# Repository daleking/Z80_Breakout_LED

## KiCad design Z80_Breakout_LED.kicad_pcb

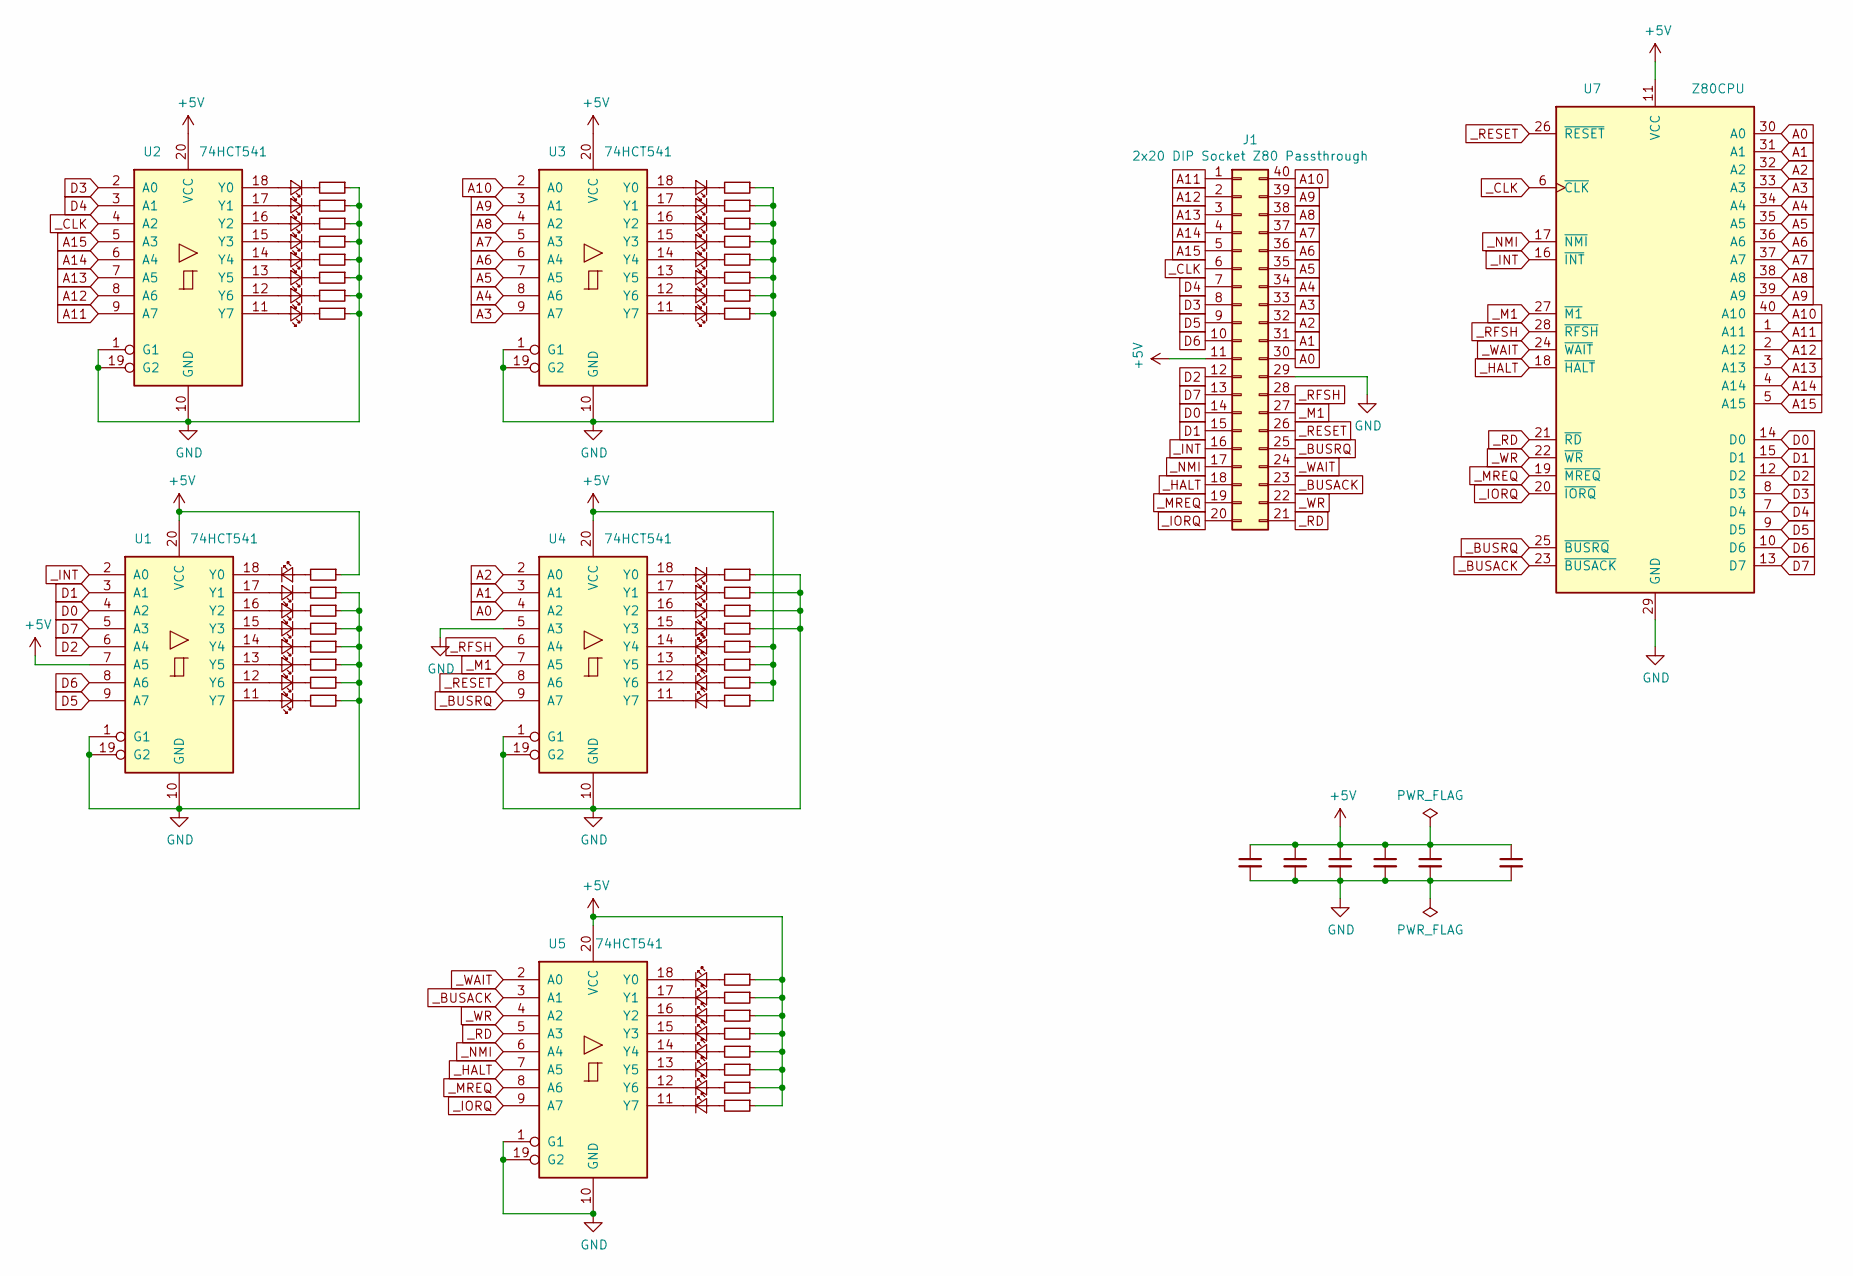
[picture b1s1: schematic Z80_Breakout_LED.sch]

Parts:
C1, C2, C3, C4, C5, C6: C_Small; C_Disc_D3.0mm_W2.0mm_P2.50mm
D1, D2, D3, D4, D5, D6, D7, D8, D9, D10, D11, D12, D13, D14, D15, D16, D17, D18, D19, D20, D21, D22, D23, D24, D25, D26, D27, D28, D29, D30, D31, D32, D33, D34, D35, D36, D37, D38, D39, D40: LED_Small; LED_D5.0mm
J1: 2x20 DIP Socket Z80 Passthrough; DIP-40_W15.24mm
R1, R2, R3, R4, R5, R6, R7, R8, R9, R10, R11, R12, R13, R14, R15, R16, R17, R18, R19, R20, R21, R22, R23, R24, R25, R26, R27, R28, R29, R30, R31, R32, R33, R34, R35, R36, R37, R38, R39, R40: R_Small; R_Axial_DIN0207_L6.3mm_D2.5mm_P10.16mm_Horizontal
U1, U2, U3, U4, U5: 74HCT541; DIP-20_W7.62mm_Socket
U7: Z80CPU; DIP-40_W15.24mm_Socket

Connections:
+5V: C1.1, C2.1, C3.1, C4.1, C5.1, C6.1, J1.11, R1.1, R29.1, R30.1, R31.1, R32.1, R33.1, R34.1, R35.1, R36.1, R37.1, R38.1, R39.1, R40.1, U1.7 (A5), U1.20 (VCC), U2.20 (VCC), U3.20 (VCC), U4.20 (VCC), U5.20 (VCC), U7.11 (VCC)
A0: J1.30, U4.4 (A2), U7.30 (A0)
A1: J1.31, U4.3 (A1), U7.31 (A1)
A2: J1.32, U4.2 (A0), U7.32 (A2)
A3: J1.33, U3.9 (A7), U7.33 (A3)
A4: J1.34, U3.8 (A6), U7.34 (A4)
A5: J1.35, U3.7 (A5), U7.35 (A5)
A6: J1.36, U3.6 (A4), U7.36 (A6)
A7: J1.37, U3.5 (A3), U7.37 (A7)
A8: J1.38, U3.4 (A2), U7.38 (A8)
A9: J1.39, U3.3 (A1), U7.39 (A9)
A10: J1.40, U3.2 (A0), U7.40 (A10)
A11: J1.1, U2.9 (A7), U7.1 (A11)
A12: J1.2, U2.8 (A6), U7.2 (A12)
A13: J1.3, U2.7 (A5), U7.3 (A13)
A14: J1.4, U2.6 (A4), U7.4 (A14)
A15: J1.5, U2.5 (A3), U7.5 (A15)
D0: J1.14, U1.4 (A2), U7.14 (D0)
D1: J1.15, U1.3 (A1), U7.15 (D1)
D2: J1.12, U1.6 (A4), U7.12 (D2)
D3: J1.8, U2.2 (A0), U7.8 (D3)
D4: J1.7, U2.3 (A1), U7.7 (D4)
D5: J1.9, U1.9 (A7), U7.9 (D5)
D6: J1.10, U1.8 (A6), U7.10 (D6)
D7: J1.13, U1.5 (A3), U7.13 (D7)
GND: C1.2, C2.2, C3.2, C4.2, C5.2, C6.2, J1.29, R2.1, R3.1, R4.1, R5.1, R6.1, R7.1, R8.1, R9.1, R10.1, R11.1, R12.1, R13.1, R14.1, R15.1, R16.1, R17.1, R18.1, R19.1, R20.1, R21.1, R22.1, R23.1, R24.1, R25.1, R26.1, R27.1, R28.1, U1.1 (G1), U1.10 (GND), U1.19 (G2), U2.1 (G1), U2.10 (GND), U2.19 (G2), U3.1 (G1), U3.10 (GND), U3.19 (G2), U4.1 (G1), U4.5 (A3), U4.10 (GND), U4.19 (G2), U5.1 (G1), U5.10 (GND), U5.19 (G2), U7.29 (GND)
unnamed: D1.1 (K), U1.18 (Y0)
unnamed: D1.2 (A), R1.2
unnamed: D2.1 (K), R2.2
unnamed: D2.2 (A), U1.17 (Y1)
unnamed: D3.1 (K), R3.2
unnamed: D3.2 (A), U1.16 (Y2)
unnamed: D4.1 (K), R4.2
unnamed: D4.2 (A), U1.15 (Y3)
unnamed: D5.1 (K), R5.2
unnamed: D5.2 (A), U1.14 (Y4)
unnamed: D6.1 (K), R6.2
unnamed: D6.2 (A), U1.13 (Y5)
unnamed: D7.1 (K), R7.2
unnamed: D7.2 (A), U1.12 (Y6)
unnamed: D8.1 (K), R8.2
unnamed: D8.2 (A), U1.11 (Y7)
unnamed: D9.1 (K), R9.2
unnamed: D9.2 (A), U2.18 (Y0)
unnamed: D10.1 (K), R10.2
unnamed: D10.2 (A), U2.17 (Y1)
unnamed: D11.1 (K), R11.2
unnamed: D11.2 (A), U2.16 (Y2)
unnamed: D12.1 (K), R12.2
unnamed: D12.2 (A), U2.15 (Y3)
unnamed: D13.1 (K), R13.2
unnamed: D13.2 (A), U2.14 (Y4)
unnamed: D14.1 (K), R14.2
unnamed: D14.2 (A), U2.13 (Y5)
unnamed: D15.1 (K), R15.2
unnamed: D15.2 (A), U2.12 (Y6)
unnamed: D16.1 (K), R16.2
unnamed: D16.2 (A), U2.11 (Y7)
unnamed: D17.1 (K), R17.2
unnamed: D17.2 (A), U3.18 (Y0)
unnamed: D18.1 (K), R18.2
unnamed: D18.2 (A), U3.17 (Y1)
unnamed: D19.1 (K), R19.2
unnamed: D19.2 (A), U3.16 (Y2)
unnamed: D20.1 (K), R20.2
unnamed: D20.2 (A), U3.15 (Y3)
unnamed: D21.1 (K), R21.2
unnamed: D21.2 (A), U3.14 (Y4)
unnamed: D22.1 (K), R22.2
unnamed: D22.2 (A), U3.13 (Y5)
unnamed: D23.1 (K), R23.2
unnamed: D23.2 (A), U3.12 (Y6)
unnamed: D24.1 (K), R24.2
unnamed: D24.2 (A), U3.11 (Y7)
unnamed: D25.1 (K), R25.2
unnamed: D25.2 (A), U4.18 (Y0)
unnamed: D26.1 (K), R26.2
unnamed: D26.2 (A), U4.17 (Y1)
unnamed: D27.1 (K), R27.2
unnamed: D27.2 (A), U4.16 (Y2)
unnamed: D28.1 (K), R28.2
unnamed: D28.2 (A), U4.15 (Y3)
unnamed: D29.1 (K), U4.14 (Y4)
unnamed: D29.2 (A), R29.2
unnamed: D30.1 (K), U4.13 (Y5)
unnamed: D30.2 (A), R30.2
unnamed: D31.1 (K), U4.12 (Y6)
unnamed: D31.2 (A), R31.2
unnamed: D32.1 (K), U4.11 (Y7)
unnamed: D32.2 (A), R32.2
unnamed: D33.1 (K), U5.18 (Y0)
unnamed: D33.2 (A), R33.2
unnamed: D34.1 (K), U5.17 (Y1)
unnamed: D34.2 (A), R34.2
unnamed: D35.1 (K), U5.16 (Y2)
unnamed: D35.2 (A), R35.2
unnamed: D36.1 (K), U5.15 (Y3)
unnamed: D36.2 (A), R36.2
unnamed: D37.1 (K), U5.14 (Y4)
unnamed: D37.2 (A), R37.2
unnamed: D38.1 (K), U5.13 (Y5)
unnamed: D38.2 (A), R38.2
unnamed: D39.1 (K), U5.12 (Y6)
unnamed: D39.2 (A), R39.2
unnamed: D40.1 (K), U5.11 (Y7)
unnamed: D40.2 (A), R40.2
_BUSACK: J1.23, U5.3 (A1), U7.23 (~BUSACK~)
_BUSRQ: J1.25, U4.9 (A7), U7.25 (~BUSRQ~)
_CLK: J1.6, U2.4 (A2), U7.6 (~CLK~)
_HALT: J1.18, U5.7 (A5), U7.18 (~HALT~)
_INT: J1.16, U1.2 (A0), U7.16 (~INT~)
_IORQ: J1.20, U5.9 (A7), U7.20 (~IORQ~)
_M1: J1.27, U4.7 (A5), U7.27 (~M1~)
_MREQ: J1.19, U5.8 (A6), U7.19 (~MREQ~)
_NMI: J1.17, U5.6 (A4), U7.17 (~NMI~)
_RD: J1.21, U5.5 (A3), U7.21 (~RD~)
_RESET: J1.26, U4.8 (A6), U7.26 (~RESET~)
_RFSH: J1.28, U4.6 (A4), U7.28 (~RFSH~)
_WAIT: J1.24, U5.2 (A0), U7.24 (~WAIT~)
_WR: J1.22, U5.4 (A2), U7.22 (~WR~)

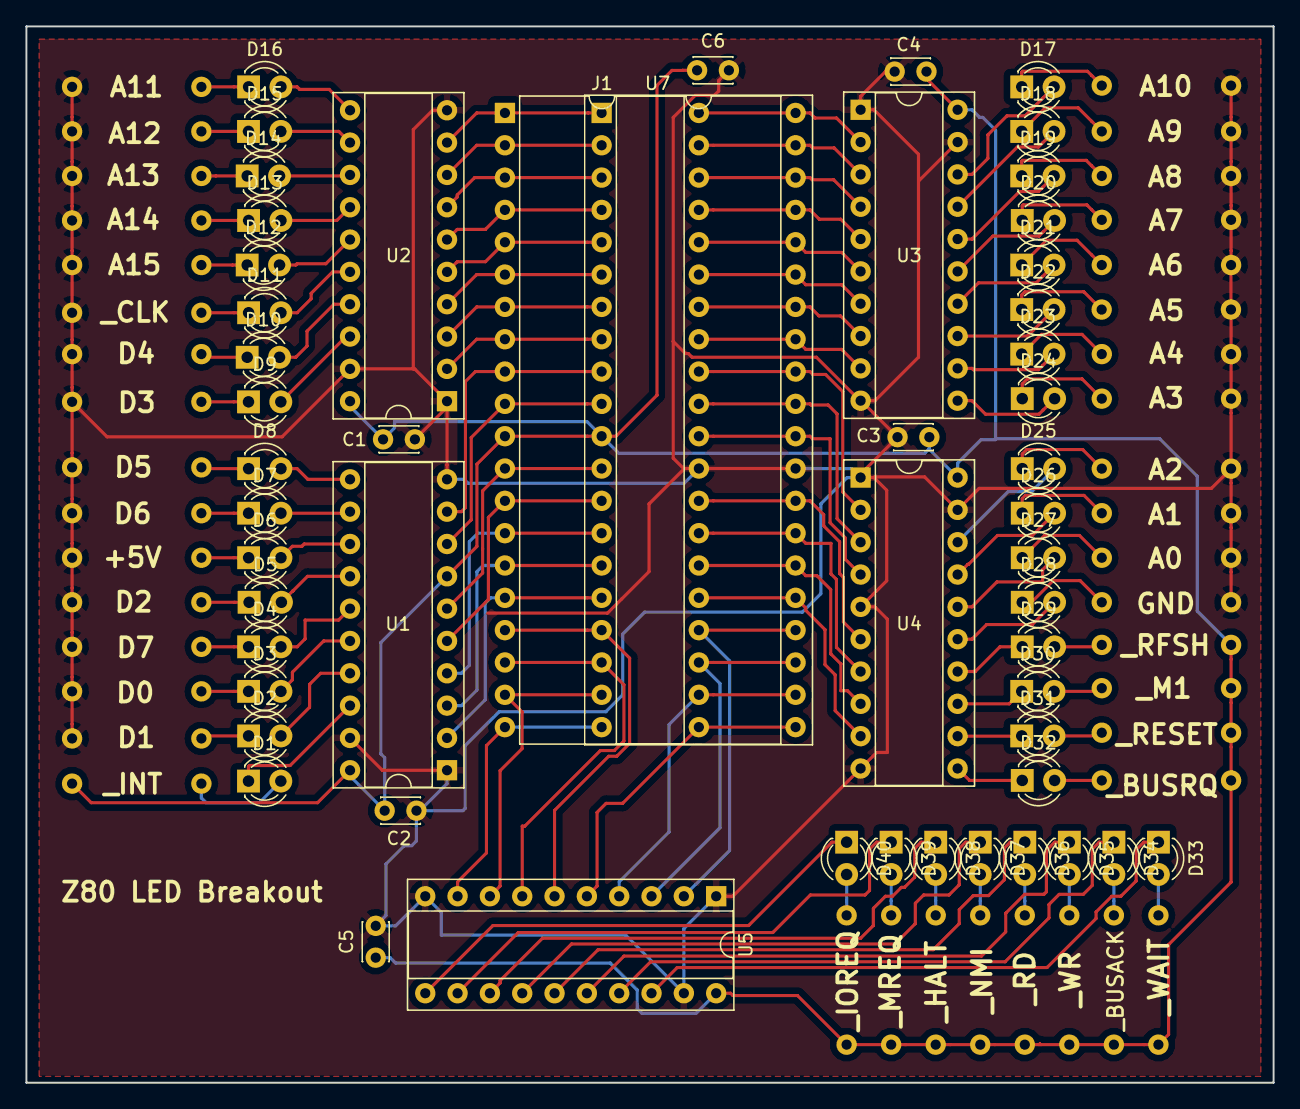
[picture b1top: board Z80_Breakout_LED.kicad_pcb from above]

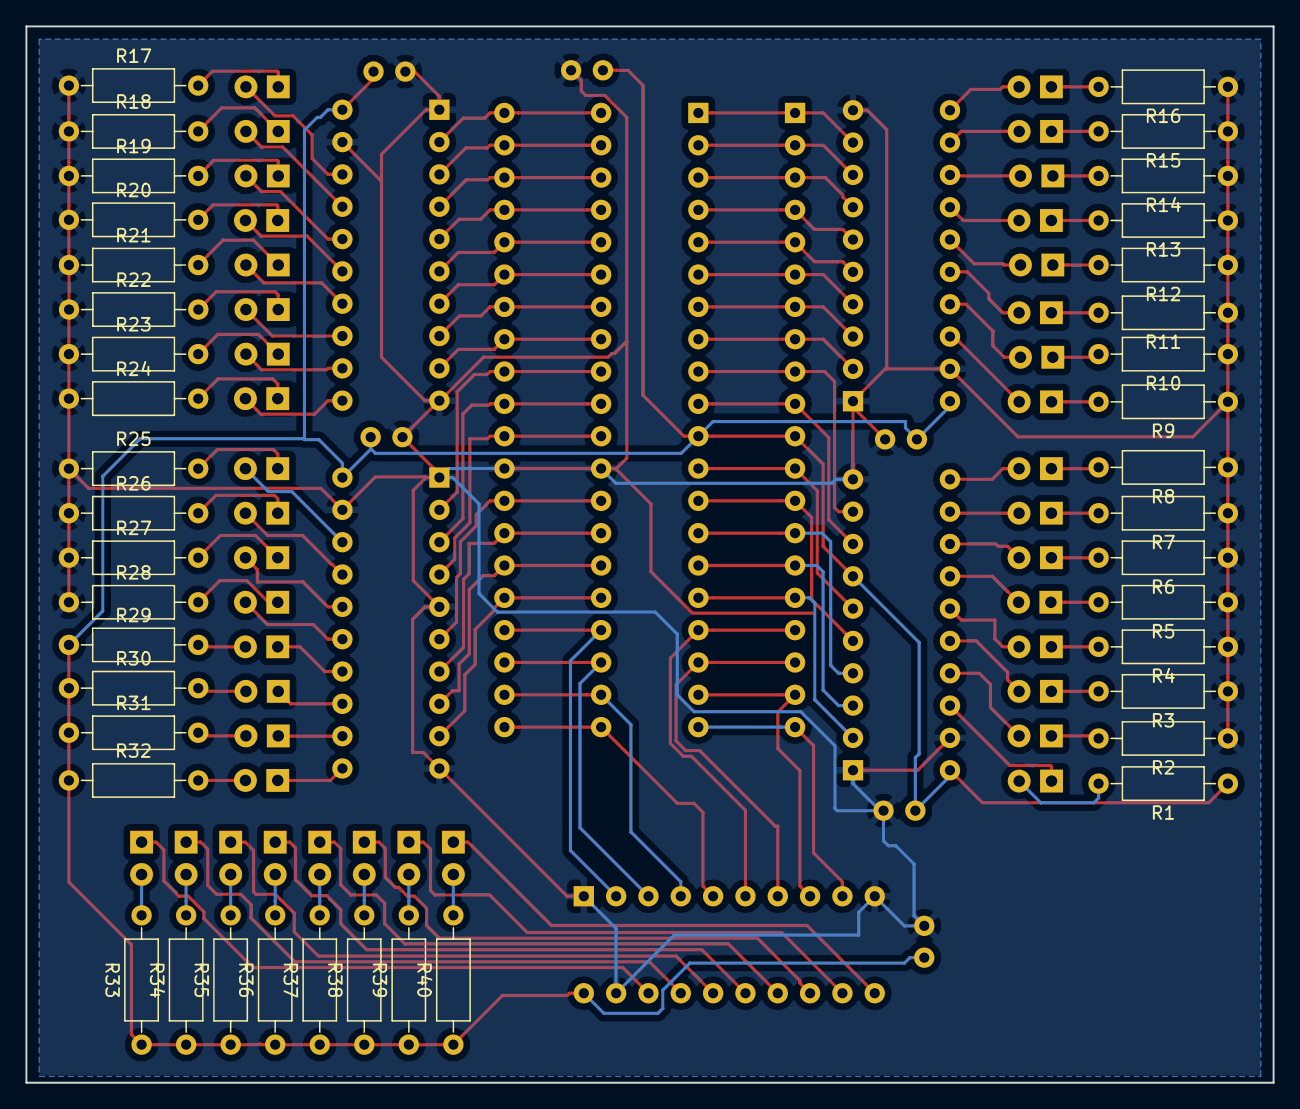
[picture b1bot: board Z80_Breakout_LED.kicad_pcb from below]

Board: 2 copper layers, 98.0 x 83.0 mm, 93 parts (40 on the bottom side), 120 nets.

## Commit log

2019-03-17 first try - untested!
2019-03-17 add board and schematic
